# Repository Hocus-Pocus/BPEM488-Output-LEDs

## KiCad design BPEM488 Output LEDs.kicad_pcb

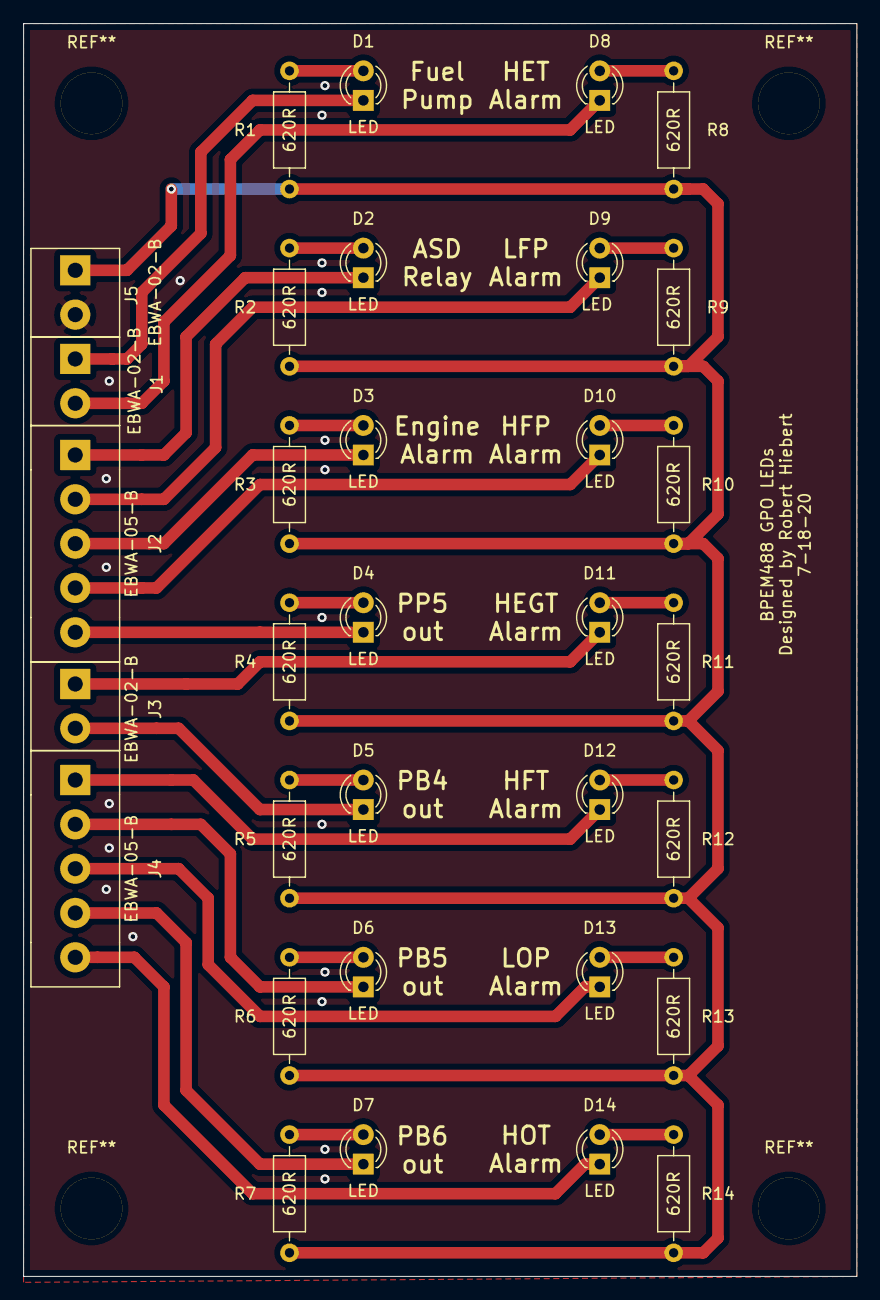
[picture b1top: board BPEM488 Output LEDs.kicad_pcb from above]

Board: 2 copper layers, 71.6 x 107.7 mm, 33 parts (0 on the bottom side), 29 nets.

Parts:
D1, D2, D3, D4, D5, D6, D7, D8, D9, D10, D11, D12, D13, D14: LED; LED_D3.0mm
J1, J3, J5: EBWA-02-B
J2, J4: EBWA-05-B
R1, R2, R3, R4, R5, R6, R7, R8, R9, R10, R11, R12, R13, R14: 620R; R_Axial_DIN0207_L6.3mm_D2.5mm_P10.16mm_Horizontal

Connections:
+12V: J5.1, R1.1, R2.1, R3.1, R4.1, R5.1, R6.1, R7.1, R8.2, R9.2, R10.2, R11.2, R12.2, R13.2, R14.2
/HEGT: D11.1, J3.1
/HET: D8.1, J1.2
/HFP: D10.1, J2.4
/HFT: D12.1, J4.1
/HOT: D13.1, J4.3
/LFP: D9.1, J2.2
/LOP: D14.1, J4.5
unnamed: D1.1, J1.1
unnamed: D1.2, R1.2
unnamed: D2.1, J2.1
unnamed: D2.2, R2.2
unnamed: D3.1, J2.3
unnamed: D3.2, R3.2
unnamed: D4.1, J2.5
unnamed: D4.2, R4.2
unnamed: D5.1, J3.2
unnamed: D5.2, R5.2
unnamed: D6.1, J4.2
unnamed: D6.2, R6.2
unnamed: D7.1, J4.4
unnamed: D7.2, R7.2
unnamed: D8.2, R8.1
unnamed: D9.2, R9.1
unnamed: D10.2, R10.1
unnamed: D11.2, R11.1
unnamed: D12.2, R12.1
unnamed: D13.2, R13.1
unnamed: D14.2, R14.1
